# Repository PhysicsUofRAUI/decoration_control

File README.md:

# decoration_control
A repo to contain the code examples and ecad documents for my Arduino shield that controls decorations or anything you want.

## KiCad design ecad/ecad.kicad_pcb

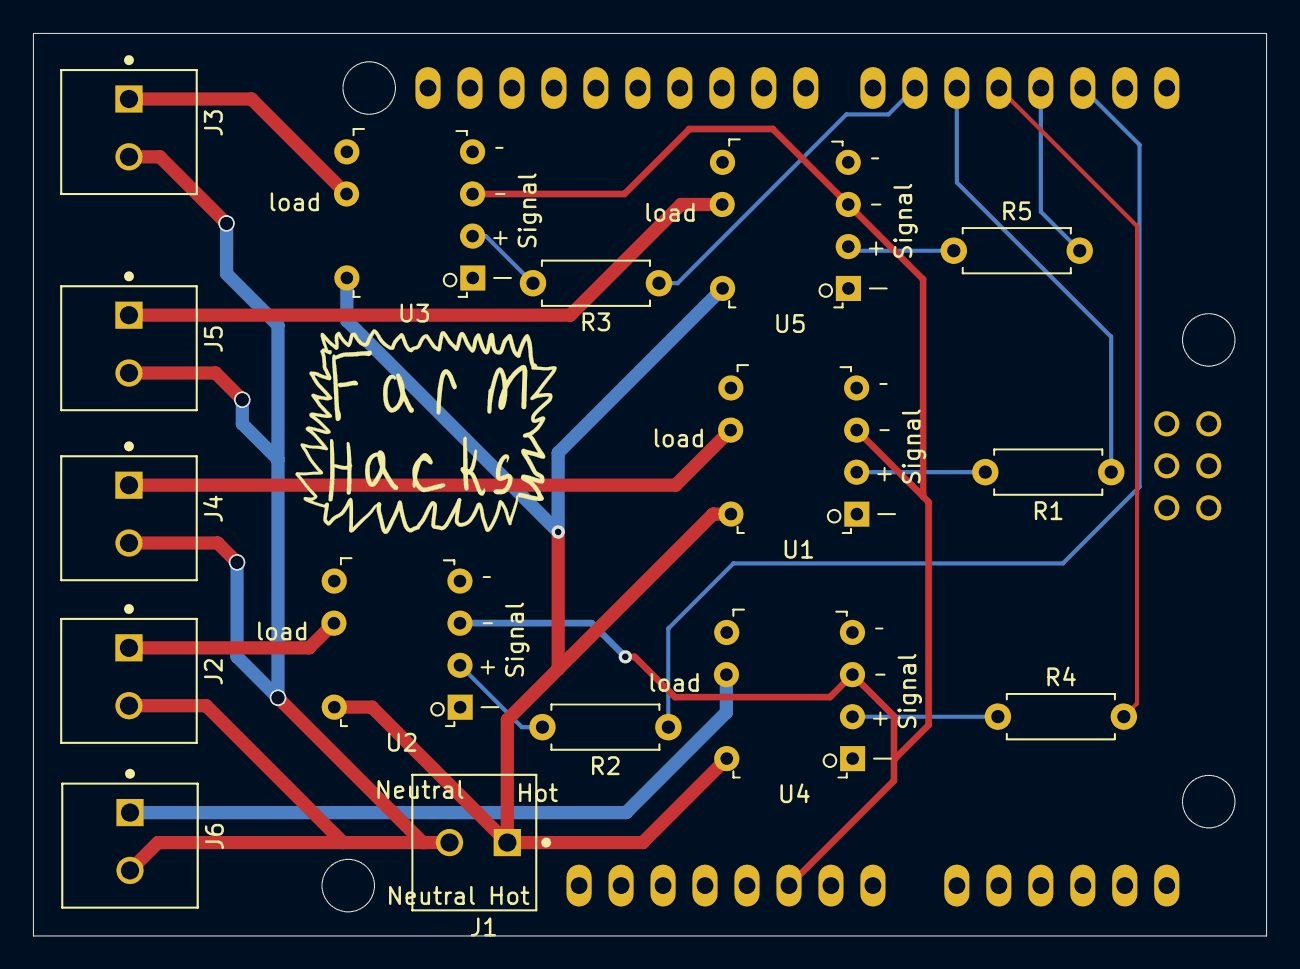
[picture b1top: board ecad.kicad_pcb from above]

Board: 2 copper layers, 74.6 x 54.6 mm, 17 parts (0 on the bottom side), 18 nets.

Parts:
J1: 284391-2; TE_284391-2
J2: Pin 2; TE_284391-2
J3: Pin 6; TE_284391-2
J4: Pin 5; TE_284391-2
J5: Pin 3; TE_284391-2
J6: Pin 4; TE_284391-2
R1, R2, R3, R4, R5: 220; R_Axial_DIN0207_L6.3mm_D2.5mm_P7.62mm_Horizontal
SHIELD1: ARDUINO_SHIELD
U1, U2, U3, U4, U5: AQH_relay; AHQ_relay

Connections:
AC: J1.1, U1.8, U2.8, U3.8, U4.8, U5.8
GND: SHIELD1.GND1, U1.3, U2.3, U3.3, U4.3, U5.3
NEUT: J1.2, J2.2, J3.2, J4.2, J5.2, J6.2
unnamed: J2.1, U2.6
unnamed: J3.1, U3.6
unnamed: J4.1, U1.6
unnamed: J5.1, U5.6
unnamed: J6.1, U4.6
unnamed: R1.1, SHIELD1.5
unnamed: R1.2, U1.2
unnamed: R2.1, SHIELD1.2
unnamed: R2.2, U2.2
unnamed: R3.1, SHIELD1.6
unnamed: R3.2, U3.2
unnamed: R4.1, U4.2
unnamed: R4.2, SHIELD1.4
unnamed: R5.1, U5.2
unnamed: R5.2, SHIELD1.3

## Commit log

2021-09-18 add first example
2021-09-19 add gitignore file
2021-09-19 fix typo in gitignore
2021-09-19 add first draft of pcb files
2021-10-24 update ecad
2021-10-24 add new 5 decoration control
2021-10-29 add another decoration control example
2021-12-17 Add code that is currently (17/12/2021) running on the Christmas lights
